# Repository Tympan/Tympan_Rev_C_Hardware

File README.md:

# Tympan_Rev_C_Hardware
Repository for the board files for Tympan Rev C

These design files were made with [KiCAD](http://kicad-pcb.org/) PCB capture software. The custom component files for parts used in this design are located in the repo as well. Everything should render correctly in the Schematic and the PCB. If not, you may need to adjust the library paths. 

This work is based on work done by Creare and their team in Spring of 2017. Modifications have been made to their Rev A hardware design to overcome bugs and improve the design. 

## Works with Teensy 3.6
The [Teensy 3.6](https://www.pjrc.com/store/teensy36.html) from PJRC is the 'brain' that drives our audio board. In order to make the Tympan and the Teensy live happily together, you will need to modify the Teensy board as shown.

The change allows us to use the VUSB (5V) to charge the LiIon battery with circuitry on the Tympan. That's it! Follow the [getting started guide](https://www.pjrc.com/teensy/first_use.html) for the Teensy, and then you will be up and running with our [Tympan Library](https://github.com/Tympan/Tympan_Library) for Arduino!

## Enclosure
The Tympan Case is 3D printed, and the design files can be found [here](https://github.com/Tympan/Tympan_Rev_C_Hardware/tree/master/Enclosure) There is also a Bill of Materials that will list the screws and threaded inserts that we used.

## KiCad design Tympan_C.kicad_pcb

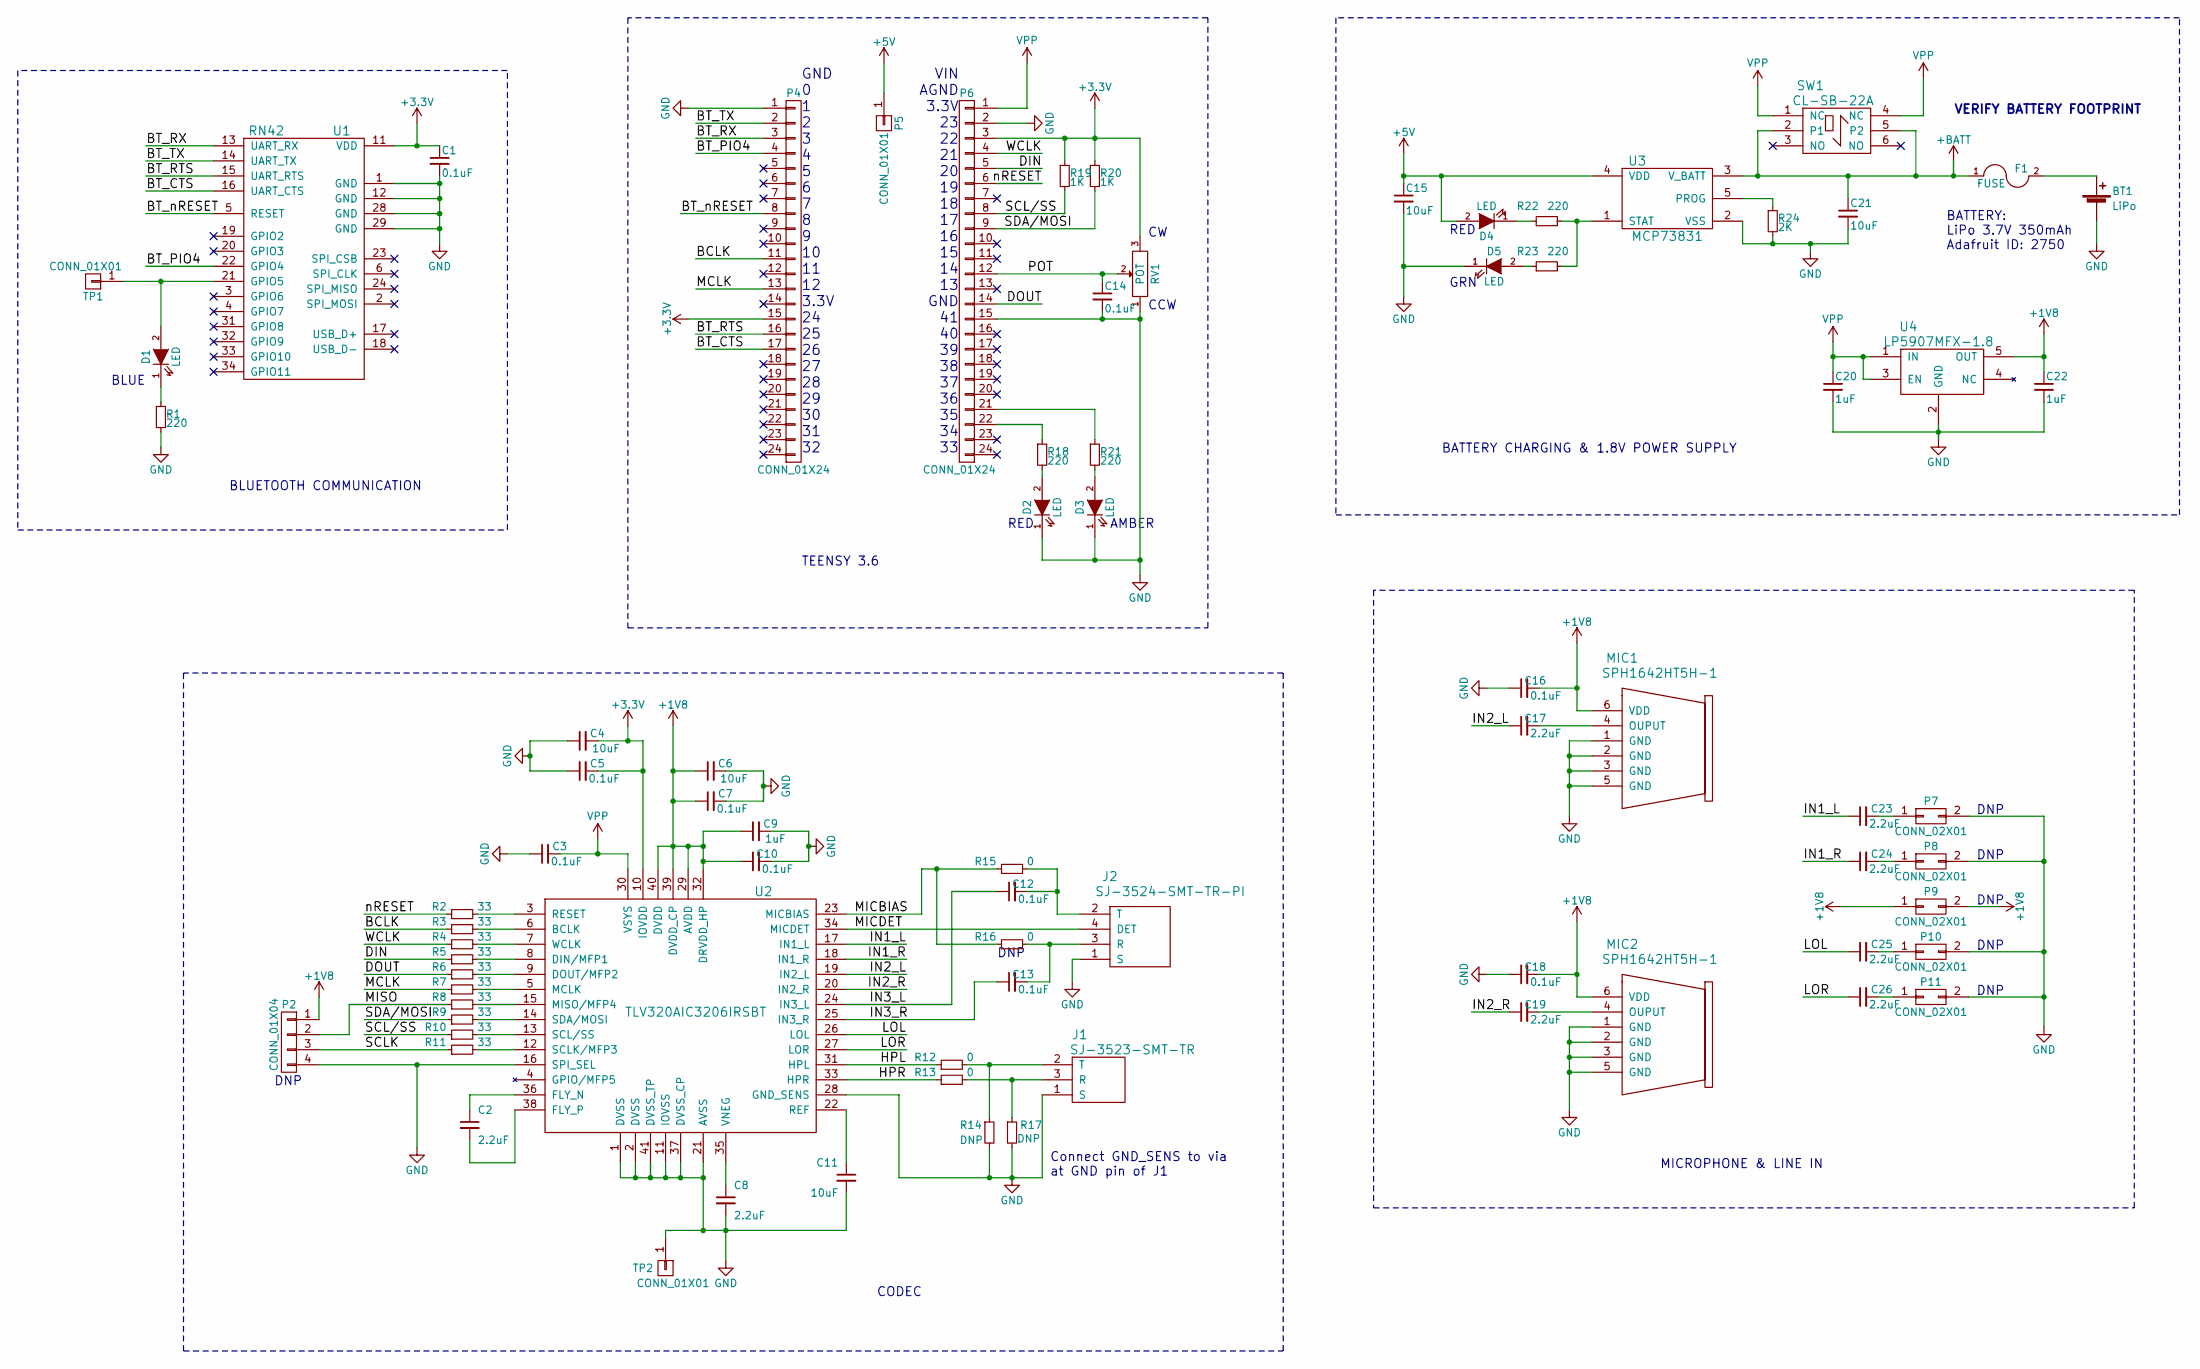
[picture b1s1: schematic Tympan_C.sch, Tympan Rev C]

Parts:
BT1: LiPo; JST_PH_B2B-PH-K_02x2.00mm_Straight
C1, C3, C5, C7, C10, C12, C13, C14, C16, C18: 0.1uF; C_0402
C2, C8, C17, C19, C23, C24, C25, C26: 2.2uF; C_0402
C4, C6, C11, C15, C21: 10uF; C_0402
C9, C20, C22: 1uF; C_0402
D1, D2, D3, D4, D5: LED; C_1206
F1: FUSE; C_1206
J1: SJ-3523-SMT-TR
J2: SJ-3524-SMT-TR-PI; SJ-3524-SMT-TR
MIC1, MIC2: SPH1642HT5H-1; SPH1642HT5H
P2: CONN_01X04; Pin_Header_Straight_1x04_Pitch2.54mm
P4, P6: CONN_01X24; Pin_Header_Straight_1x24_Pitch2.54mm
P5: CONN_01X01; Pin_Header_Straight_1x01_Pitch2.54mm
P7, P8, P9, P10, P11: CONN_02X01; Pin_Header_Straight_1x02_Pitch2.54mm
R1, R18, R21, R22, R23: 220; R_0402
R2, R3, R4, R5, R6, R7, R8, R9, R10, R11: 33; R_0201_NoSilk
R12, R13, R15, R16: 0; C_0603
R14, R17: DNP; C_0603
R19, R20: 1K; R_0402
R24: 2K; R_0402
RV1: POT; Bourns_3386F
SW1: CL-SB-22A
TP1, TP2: CONN_01X01; Pin_Header_Straight_1x01_Pitch2.54mm
U1: RN42
U2: TLV320AIC3206IRSBT; UQFN-40-1EP_5x5mm_Pitch0.4mm
U3: MCP73831; SOT-23-5
U4: LP5907MFX-1.8; SOT-23-5

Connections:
+1V8: C6.1, C7.1, C9.1, C10.1, C16.2, C18.2, C22.1, MIC1.6 (VDD), MIC2.6 (VDD), P2.1, P9.1, P9.2, U2.29 (AVDD), U2.32 (DRVDD_HP), U2.39 (DVDD_CP), U2.40 (DVDD), U4.5 (OUT)
+3V3: C1.1, C4.2, C5.2, P4.15, P6.3, R19.1, R20.1, RV1.3, U1.11 (VDD), U2.10 (IOVDD)
+5V: C15.1, D4.2 (A), P5.1, U3.4 (VDD)
+BATT: C21.1, F1.1, SW1.2 (P1), SW1.5 (P2), U3.3 (V_BATT)
/BCLK: P4.11, R3.1
/BT_CTS: P4.17, U1.16 (UART_CTS)
/BT_PIO4: P4.4, U1.22 (GPIO4)
/BT_RTS: P4.16, U1.15 (UART_RTS)
/BT_RX: P4.3, U1.13 (UART_RX)
/BT_TX: P4.2, U1.14 (UART_TX)
/BT_nRESET: P4.8, U1.5 (RESET)
/DIN: P6.5, R5.1
/DOUT: P6.14, R6.1
/HPL: R12.1, U2.31 (HPL)
/HPR: R13.1, U2.33 (HPR)
/IN1_L: C23.1, U2.17 (IN1_L)
/IN1_R: C24.1, U2.18 (IN1_R)
/IN2_L: C17.1, U2.19 (IN2_L)
/IN2_R: C19.1, U2.20 (IN2_R)
/IN3_L: C12.1, U2.24 (IN3_L)
/IN3_R: C13.1, U2.25 (IN3_R)
/LOL: C25.1, U2.26 (LOL)
/LOR: C26.1, U2.27 (LOR)
/MCLK: P4.13, R7.1
/MICBIAS: R15.1, R16.1, U2.23 (MICBIAS)
/MICDET: J2.4 (DET), U2.34 (MICDET)
/MISO: P2.2, R8.1
/POT: C14.1, P6.12, RV1.2
/SCL/SS: P6.8, R10.1, R19.2
/SCLK: P2.3, R11.1
/SDA/MOSI: P6.9, R9.1, R20.2
/WCLK: P6.4, R4.1
/nRESET: P6.6, R2.1
GND: BT1.2 (-), C1.2, C3.1, C4.1, C5.1, C6.2, C7.2, C8.2, C9.2, C10.2, C11.2, C14.2, C15.2, C16.1, C18.1, C20.2, C21.2, C22.2, D2.1 (K), D3.1 (K), D5.1 (K), J1.1 (S), J2.1 (S), MIC1.1 (GND), MIC1.2 (GND), MIC1.3 (GND), MIC1.5 (GND), MIC2.1 (GND), MIC2.2 (GND), MIC2.3 (GND), MIC2.5 (GND), P2.4, P4.1, P6.2, P6.15, P7.2, P8.2, P10.2, P11.2, R1.2, R14.2, R17.2, R24.2, RV1.1, TP2.1, U1.1 (GND), U1.12 (GND), U1.28 (GND), U1.29 (GND), U2.1 (DVSS), U2.2 (DVSS), U2.11 (IOVSS), U2.16 (SPI_SEL), U2.21 (AVSS), U2.28 (GND_SENS), U2.37 (DVSS_CP), U2.41 (DVSS_TP), U3.2 (VSS), U4.2 (GND)
unnamed: BT1.1 (+), F1.2
unnamed: C2.1, U2.36 (FLY_N)
unnamed: C2.2, U2.38 (FLY_P)
unnamed: C8.1, U2.35 (VNEG)
unnamed: C11.1, U2.22 (REF)
unnamed: C12.2, J2.2 (T), R15.2
unnamed: C13.2, J2.3 (R), R16.2
unnamed: C17.2, MIC1.4 (OUPUT)
unnamed: C19.2, MIC2.4 (OUPUT)
unnamed: C23.2, P7.1
unnamed: C24.2, P8.1
unnamed: C25.2, P10.1
unnamed: C26.2, P11.1
unnamed: D1.1 (K), R1.1
unnamed: D1.2 (A), TP1.1, U1.21 (GPIO5)
unnamed: D2.2 (A), R18.2
unnamed: D3.2 (A), R21.2
unnamed: D4.1 (K), R22.1
unnamed: D5.2 (A), R23.1
unnamed: J1.2 (T), R12.2, R14.1
unnamed: J1.3 (R), R13.2, R17.1
unnamed: P6.21, R21.1
unnamed: P6.22, R18.1
unnamed: R2.2, U2.3 (RESET)
unnamed: R3.2, U2.6 (BCLK)
unnamed: R4.2, U2.7 (WCLK)
unnamed: R5.2, U2.8 (DIN/MFP1)
unnamed: R6.2, U2.9 (DOUT/MFP2)
unnamed: R7.2, U2.5 (MCLK)
unnamed: R8.2, U2.15 (MISO/MFP4)
unnamed: R9.2, U2.14 (SDA/MOSI)
unnamed: R10.2, U2.13 (SCL/SS)
unnamed: R11.2, U2.12 (SCLK/MFP3)
unnamed: R22.2, R23.2, U3.1 (STAT)
unnamed: R24.1, U3.5 (PROG)
VPP: C3.2, C20.1, P6.1, SW1.1 (NC), SW1.4 (NC), U2.30 (VSYS), U4.1 (IN), U4.3 (EN)

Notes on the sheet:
VIN AGND 3.3V 23 22 21 20 19 18 17 16 15 14 13 GND 41 40 39 38 37 36 35 34 33
GND 0 1 2 3 4 5 6 7 8 9 10 11 12 3.3V 24 25 26 27 28 29 30 31 32
DNP
CW CCW
RED
AMBER
BLUE
GRN
BLUETOOTH COMMUNICATION
TEENSY 3.6
BATTERY CHARGING & 1.8V POWER SUPPLY
BATTERY: LiPo 3.7V 350mAh Adafruit ID: 2750
MICROPHONE & LINE IN
CODEC
VERIFY BATTERY FOOTPRINT
Connect GND_SENS to via at GND pin of J1

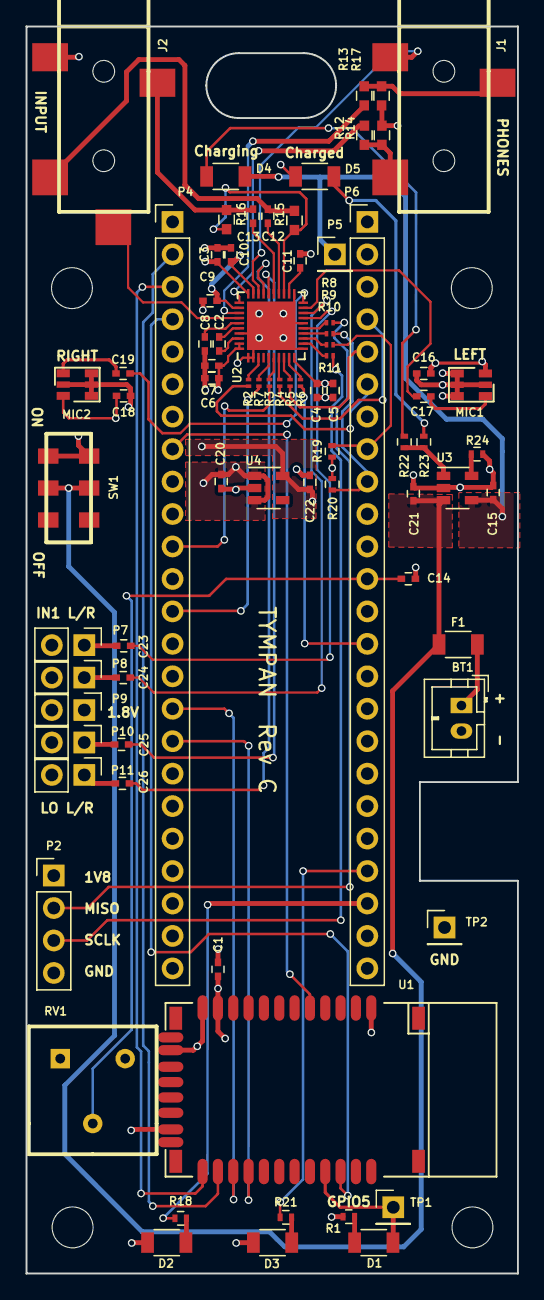
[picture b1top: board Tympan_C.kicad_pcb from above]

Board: 4 copper layers, 38.5 x 97.6 mm, 78 parts (0 on the bottom side), 70 nets.

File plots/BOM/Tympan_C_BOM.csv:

Id,Designator,Package,Quantity,Designation,Manufacturer,Part Number
1,BT1,JST_PH_B2B-PH-K_02x2.00mm_Straight,1,LiPo,JST Sales,B2B-PH-K-S(LF)(SN)
2,"D2,D4",C_1206,2,"LED, Red",Lite-On,LTST-C150EKT
3,D1,C_1206,1,"LED, Blue",Lite-On,LTST-C150TBKT
4,D3,C_1206,1,"LED, Amber",Lite-On,LTST-C150AKT
5,D5,C_1206,1,"LED, Green",Lite-On,LTST-C150GKT
6,F1,C_1206,1,FUSE,Bell Fuse,C1Q 1
7,"MIC2,MIC1",SPH1642HT5H,2,SPH1642HT5H-1,Knowles,SPH1642HT5H-1
8,"TP1,TP2",DNP,2,DNP,DNP,DNP
9,P5,Pin_Header_Straight_1x01_Pitch2.54mm,3,CONN_01X01,Samtec,SSW-101-01-G-S
10,P2,Pin_Header_Straight_1x04_Pitch2.54mm,1,CONN_01X04,Samtec,SSW-104-01-G-S
11,"P4,P6",Pin_Header_Straight_1x24_Pitch2.54mm,2,CONN_01X24,Samtec,SSW-124-01-G-S
12,"P7,P8,P9,P10,P11",DNP,5,DNP,DNP,DNP
13,"R12,R13,R15,R16",C_0603,4,0R,Vishay Dale,CRCW06030000Z0EA
14,"R14,R17",DNP,2,DNP,DNP,DNP
15,RV1,Bourns_3386F,1,POT,Bourns,3386F-1-103TLF
16,SW1,CL-SB-22A,1,CL-SB-22A,Copal,CL-SB-22A-11T
17,U1,RN42,1,RN42,Microchip,RN42-I/RM
18,U2,UQFN-40-1EP_5x5mm_Pitch0.4mm,1,TLV320AIC3206IRSBT,Texas Insturment,TLV320AIC3206IRSBT
19,U3,SOT-23-5,1,MCP73831,Microchip,MCP73831T-2ACI/OT
20,U4,SOT-23-5,1,LP5907MFX-1.8,Texas Insturment,LP5907MFX-1.8/NOPB
21,J2,SJ-3524-SMT-TR,1,SJ-3524-SMT-TR-PI,CUI Inc,SJ-3524-SMT-TR-PI
22,J1,SJ-3523-SMT-TR,1,SJ-3523-SMT-TR,CUI Inc,SJ-3523-SMT-TR
23,"C1,C3,C5,C7,C10,C12,C13,C14,C16,C18",C_0402,10,0.1uF,TDK Corporation,C1005X7R1H104K050BB
24,"C2,C8,C17,C19,C23,C24,C25,C26",C_0402,8,2.2uF,TDK Corporation,C1005X6S1C225K050BC
25,"C4,C6,C11,C15,C21",C_0402,5,10uF,Samsung,CL05A106MP5NUNC
26,"C9,C20,C22",C_0402,3,1uF,TDK Corporation,C1005X5R1C105K050BC
27,"R1,R18,R21,R22,R23",R_0402,5,220R,Vishay Dale,CRCW0402220RFKED
28,"R19,R20",R_0402,2,1K,Vishay Dale,CRCW04021K00FKED
29,R24,R_0402,1,2K,Vishay Dale,CRCW04022K00FKED
30,"R2,R3,R4,R5,R6,R7,R8,R9,R10,R11",R_0201_NoSilk,10,33R,Yageo,RC0201FR-0733RL

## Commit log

2017-08-21 Create Tympan_Rev_C
2017-08-21 Committing Design and Production files
2017-08-21 Added Schematic PDF
2017-08-24 Updated BOM
    Updated BOM to specify R16 as DNP and R15 as 2K2R
2017-08-24 Updated schematic
    changed R15 to 2.2K
    changed R16 to DNP
2017-08-29 Added print files and teensy mod
    Added info on how to mod the Teensy 3.6 and also 3D print files for the
    enclosure
2017-08-29 Added to Readme
2017-09-04 Create Hardware_Overview
2017-09-05 Added Hardware Overview
2017-09-05 Formatting
2018-03-19 fixed typos
